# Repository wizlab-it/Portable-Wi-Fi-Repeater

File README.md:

# Portable Wi-Fi Repeater

This is a battery-powered Portable Wi-Fi Repeater based on the ESP8266 board, than can be used to extend the range of a Wi-Fi Network in areas where it could be difficult to use standard Wi-Fi repeaters.

The repeater connects to the Wi-Fi Network to be extended and creates its own Wi-Fi Network. Traffic on the new Wi-Fi Network is routed through the original network.

A solar panel could be used to increase the battery life (18650 Li-ion 3.7V battery). When the battery level is low, the built-in led blinks 3 times every 15 seconds.

## Configuration Mode

When the device starts for the first time, it runs in *Configuration Mode*. An open Wi-Fi Network with SSID *PortWiFiRepeater-nnnn* (where *nnnn* is a 4-digits random number) is created.
Connecting to this network the configuration panel is shown automatically, to configure the Wi-Fi Network to extend and, optionally, the parameters of the network to create.
In the case the configuration panel is not shown automatically, open any browser and go to *http://192.168.1.1*
On the OLED display (if available) some info about the device status are shown.

The configuration panel shows the list of available Wi-Fi Networks, with details about their signal quality. The network to be extended can be selected from the list, and the PSK entered.
By default, the device creates a new Wi-Fi Network with the same SSID with the suffix "_ext", and same PSK.
Both the SSID and PSK of the new network can be customized clicking on the checkbox.
Clicking on the *Refresh* button, a new scan of the available Wi-Fi Networks is performed and the dropdown list is updated accordingly.
Clicking on the *Identify device* button, the built-in led blinks 20 times, to identify the device being configured.

When the configuration is complete, clicking on the *Save* button the parameters are saved in the local EEPROM. The led will blink fast 10 times to inform the configuration has been saved.
Rebooting the device, it will run in *Repeater Mode*.

### Configuration reset

To reset the configuration, press the button and keep it pressed when booting the device.
When the configuration has been reset the led will blink fast 10 times. If available, the OLED will show a message to inform the configuration has been removed.
After a configuration reset, the device can be configured again.

## Repeater Mode

When the device finds a valid configuration in the EEPROM during boot, it starts in *Repeater Mode*.
It first tries to connect to the original Wi-Fi Network, then it creates the new network.
Once the startup process is completed, Wi-Fi devices can connect to the new Wi-Fi Network, and their traffic will be routed automatically through the original network.
The OLED display will show some info about the original network signal quality, the number of connected stations, the battery status and the SSID of the original and new networks.
If the OLED display is not available, the signal quality of the original Wi-Fi Network can be checked pressing the button: the led will blink fast twice (to tell the signal quality will be shown), then after 1 second it will blink slow a number of times equal to the quality of the signal (0 to 5). For example, if the signal quality is 3, the led will blink twice fast, then after 1 second three times slow.

In the case the connection to the original network is lost, the device tried automatically to reconnect. On the OLED display, the *Reconnecting* message is shown.

## Credits and references

Created by [WizLab.it](https://www.wizlab.it/)

GitHub: [https://github.com/wizlab-it/temperature-monitor/](https://github.com/wizlab-it/temperature-monitor/)

[ESP8266 Documentation](https://arduino-esp8266.readthedocs.io/)

## License

This program is free software: you can redistribute it and/or modify it under the terms of the GNU General Public License as published by the Free Software Foundation, either version 3 of the License, or (at your option) any later version.

This program is distributed in the hope that it will be useful, but WITHOUT ANY WARRANTY; without even the implied warranty of MERCHANTABILITY or FITNESS FOR A PARTICULAR PURPOSE. See the GNU General Public License for more details.

To get a copy of the GNU General Public License, see [http://www.gnu.org/licenses/](http://www.gnu.org/licenses/)

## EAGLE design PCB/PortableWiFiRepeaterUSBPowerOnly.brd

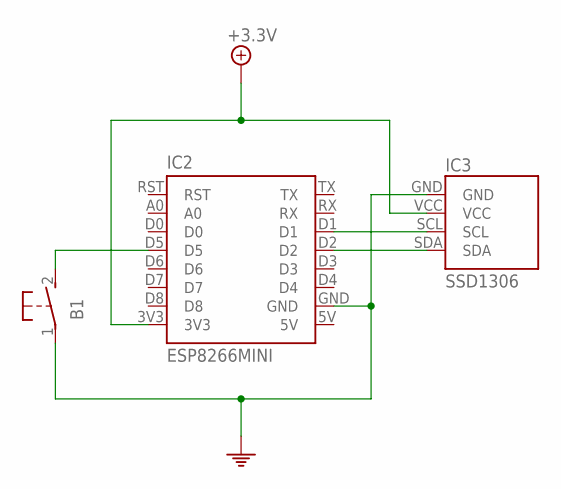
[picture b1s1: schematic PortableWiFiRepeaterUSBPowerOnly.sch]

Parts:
B1: BUTTONSIL2; SIL2
IC2: ESP8266MINI
IC3: SSD1306

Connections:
5V: IC2.5V
+3.3V: IC2.3V3, IC3.VCC
GND: B1.1, IC2.GND, IC3.GND
unnamed: B1.2 (S), IC2.D5
unnamed: IC2.D1, IC3.SCL
unnamed: IC2.D2, IC3.SDA

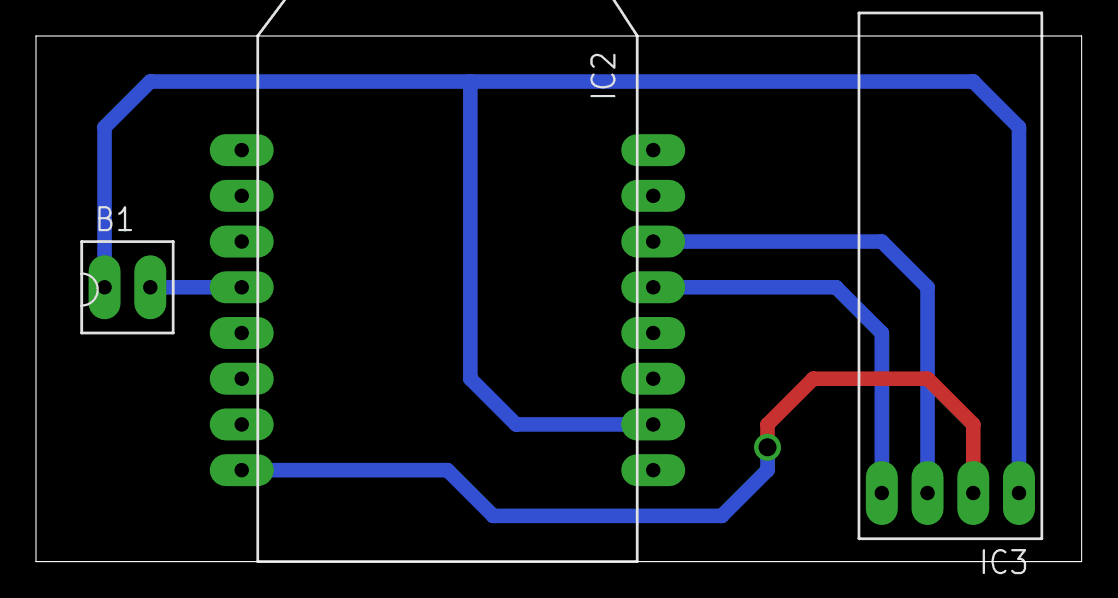
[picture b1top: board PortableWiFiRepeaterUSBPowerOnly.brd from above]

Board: 2 copper layers, 58.1 x 29.2 mm, 3 parts (0 on the bottom side), 5 nets.

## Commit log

2024-02-14 Minor fixes
2024-02-26 Minor changes
2024-09-04 External USB power supply icon
2024-10-03 Added automatic ESP restart if connection to the WiFi network to be repeated takes too long
2024-10-06 Added automatic ESP restart if reconnection to the WiFi network to be repeated takes too long
